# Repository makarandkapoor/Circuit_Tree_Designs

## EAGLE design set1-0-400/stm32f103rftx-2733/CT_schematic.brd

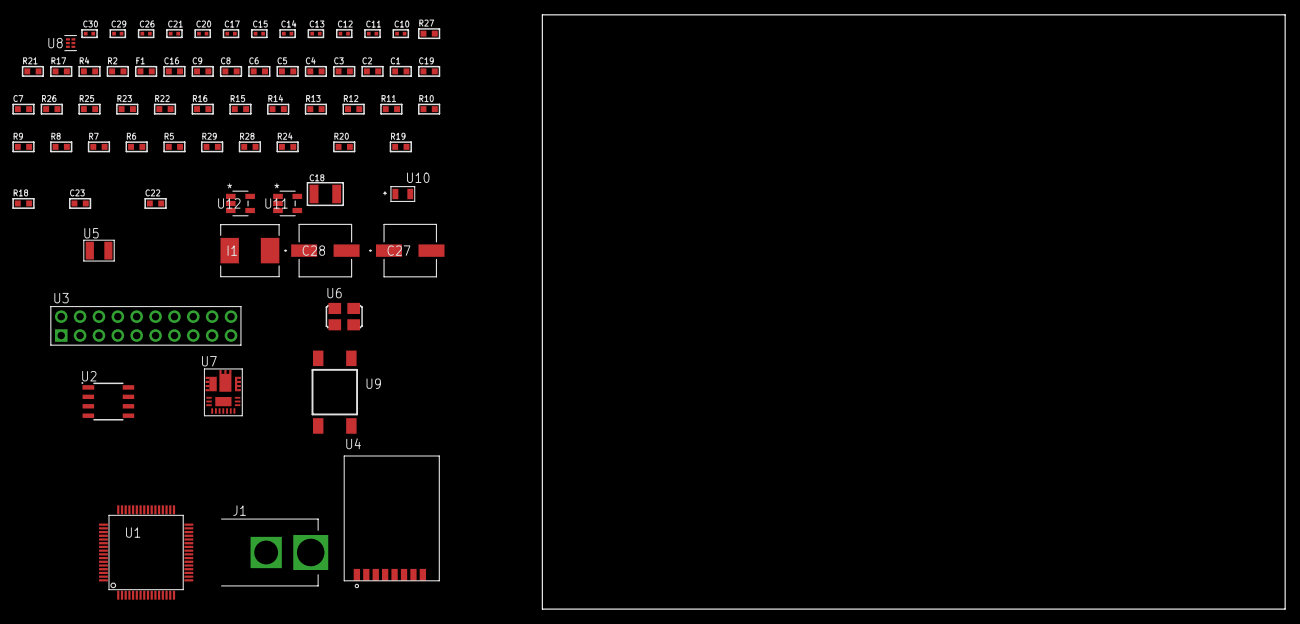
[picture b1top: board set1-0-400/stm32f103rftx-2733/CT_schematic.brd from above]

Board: 2 copper layers, 100.0 x 80.0 mm, 70 parts (0 on the bottom side), 42 nets, no tracks yet.

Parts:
C1, C9, C16: 1e-06; C0603
C2, C3, C4, C5, C6: 1e-07; C0603
C7: 4.7e-06; C0603
C8: 1e-08; C0603
C10, C11: 1e-11; C0402
C12, C17, C29, C30: 1e-08; C0402
C13, C14, C15, C20, C21, C26: 1e-07; C0402
C18: 0.0001; C1210
C19: 2.2e-06; C0603
C22: 8.6971073877236e-09; R0603
C23: 2.9649229730876e-07; R0603
C27, C28: 0.0001; EXV-9H
F1: 240.0; L0603
I1: 6.8e-07; IND25X25CZ
J1: PJ-037B; PJ-037B_PACKAGE
R2: 1000.0; R0603
R4: 4700.0; R0603
R5, R6, R7, R8, R9, R10, R11, R12, R13, R14, R15, R16, R25, R26: 10000.0; R0603
R17: 0.1; R0603
R18: 4030.2416170974; R0603
R19: 719.68600305311; R0603
R20: 58.613333333333; R0603
R21: 130.0; R0603
R22: 39000.0; R0603
R23: 49900.0; R0603
R24: 5147.5789473684; R0603
R27: 9100.0; R0603
R28: 680000.0; R0603
R29: 120000.0; R0603
U1: stm32f103rft7; LQFP64
U2: AT25M02-SSHD-T; SOIC-8
U3: TST-110-05-T-D-RA
U4: RFM75-S
U5: ABS07-32.768KHZ-7-T
U6: ASFL1-25MHZ-NCS; ASFL1
U7: IR3899MTR1PBF
U8: TPS3895ADRYR; SON-6
U9: 4-1437565-2; SW_4-1437565-2
U10: Q65110A2395; LGM67K-G1J2-24-Z
U11, U12: nc7sz125m5x; NC7SZ125M5X

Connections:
CLK_CRYSTAL_U1_3: C10.1, U1.3, U5.1
CLK_CRYSTAL_U1_4: C11.1, U1.4, U5.2
CLK_U1_5: U1.5, U6.3
GND: C1.2, C2.2, C3.2, C4.2, C5.2, C6.2, C7.2, C8.2, C9.2, C10.2, C11.2, C12.2, C13.2, C14.2, C15.2, C16.2, C17.2, C19.2, C20.2, C21.2, C26.2, C27.2, C28.2, C29.2, C30.2, J1.2, R2.2, R5.2, R14.2, R17.1, R17.2, R19.2, R22.2, R24.2, R27.2, R29.2, U1.12, U1.18, U1.31, U1.47, U1.63, U2.4, U3.4, U3.6, U3.8, U3.10, U3.12, U3.14, U3.16, U3.18, U3.20, U4.1, U6.2, U7.4, U7.11, U7.17, U8.2, U10.C, U11.2, U11.3, U12.1, U12.3
NET_U1_7: R4.1, U1.7, U12.4
NET_U1_13: C8.1, C9.1, F1.1, U1.13
NET_U1_60: R5.1, U1.60
NET_U1_62: U9.3, U9.4
NET_U2_3: R6.1, U2.3
NET_U2_7: R8.1, U2.7
NET_U3_3: R9.1, U3.3
NET_U3_7: R11.1, U3.7
NET_U3_9: R12.1, U3.9
NET_U3_19: R14.1, U3.19
NET_U4_3: R15.1, U4.3
NET_U7_1: C22.1, R18.1, R19.1, R20.1, R21.1, U7.1, U7.8
NET_U7_2: C21.1, U7.2
NET_U7_3: C22.2, C23.1, C23.2, U7.3
NET_U7_5: R22.1, U7.5
NET_U7_10: C19.1, U7.10
NET_U7_12: C18.1, I1.1, U7.12
NET_U7_14: C18.2, U7.14
NET_U7_15: R23.1, R24.1, U7.15
NET_U7_ATNET_3: I1.2, R18.2
NET_U7_ATNET_4: C23.2, R20.2
NET_U8_1: R26.1, R27.1, U8.1
NET_U8_3: R28.2, R29.1, U8.3
NET_U8_4: R25.1, U8.4, U11.4, U12.2
NET_U9_1: R2.1, U9.1, U9.2
PROC_SPI1_MISO: U1.22, U4.7
PROC_SPI1_MOSI: U1.23, U4.6
PROC_SPI1_NSS: R16.1, U1.20, U4.4
PROC_SPI1_SCK: U1.21, U4.5
PROC_SPI2_MISO: U1.35, U2.2
PROC_SPI2_MOSI: U1.36, U2.5
PROC_SPI2_NSS: R7.1, U1.33, U2.1
PROC_SPI2_SCK: U1.34, U2.6
PROC_SYS_JTDI: R10.1, U1.50, U3.5
PROC_SYS_JTDO_TRACESWO: U1.55, U3.13
RST_OUT_U3_SRESET_B: R13.1, U3.15, U11.1
VCC_S1_16V8: C20.1, C27.1, C28.1, J1.1, R23.2, U7.9
VCC_TIER1_3V3: C1.1, C2.1, C3.1, C4.1, C5.1, C6.1, C7.1, C12.1, C13.1, C14.1, C15.1, C16.1, C17.1, C26.1, C29.1, C30.1, F1.2, I1.2, R4.2, R6.2, R7.2, R8.2, R9.2, R10.2, R11.2, R12.2, R13.2, R15.2, R16.2, R18.2, R25.2, R26.2, R28.1, U1.1, U1.19, U1.32, U1.48, U1.64, U2.8, U3.1, U3.2, U4.2, U6.4, U8.6, U11.5, U12.5

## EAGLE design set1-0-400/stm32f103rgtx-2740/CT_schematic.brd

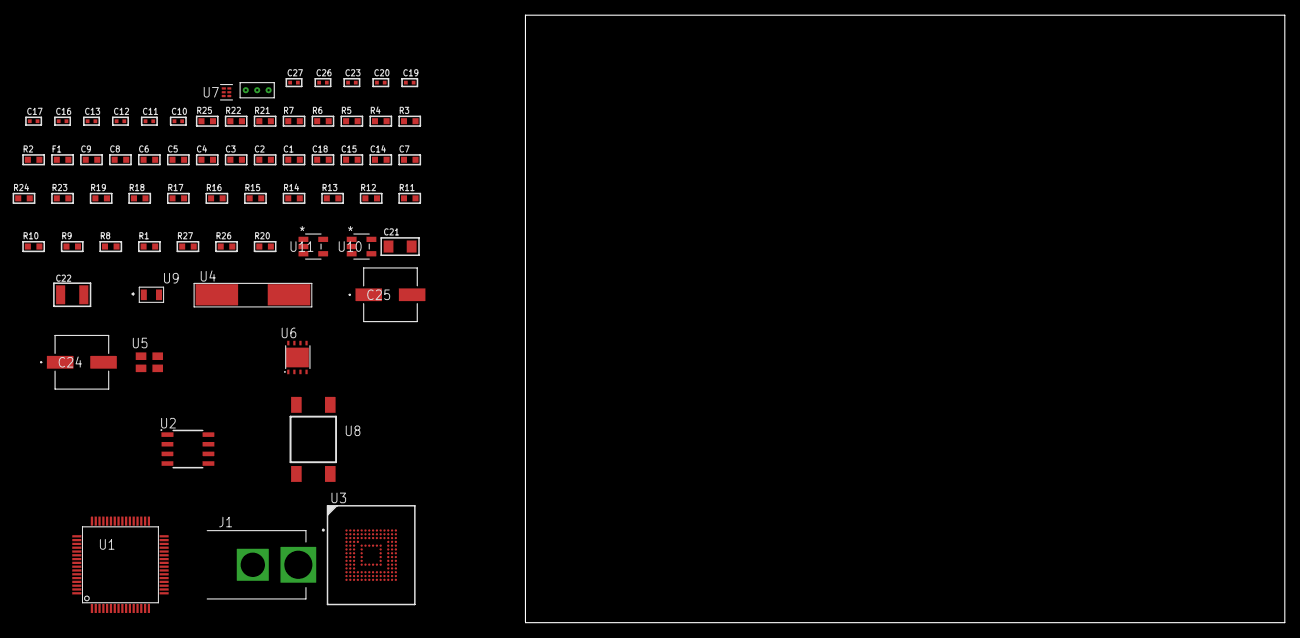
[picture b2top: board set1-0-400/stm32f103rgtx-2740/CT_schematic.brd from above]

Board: 2 copper layers, 100.0 x 80.0 mm, 68 parts (0 on the bottom side), 35 nets, no tracks yet.

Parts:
C1, C9: 1e-06; C0603
C2, C3, C4, C5, C6: 1e-07; C0603
C7: 4.7e-06; C0603
C8: 1e-08; C0603
C10, C11: 1e-11; C0402
C12, C19, C20, C26, C27: 1e-08; C0402
C13, C16, C17, C23: 1e-07; C0402
C14, C15, C18: 2.2e-06; C0603
C21: 1e-05; C1206
C22: 1e-05; C1210
C24, C25: 0.0001; EXV-9H
F1: 240.0; L0603
J1: PJ-037B; PJ-037B_PACKAGE
R1, R8, R9, R23, R24: 10000.0; R0603
R2, R22: 1000.0; R0603
R3: 1600.5; R0603
R4, R5: 4700.0; R0603
R6, R7: 2200.0; R0603
R10, R11, R12, R13, R14, R15, R16, R17, R18, R19: 34000.0; R0603
R20: 100000.0; R0603
R21: 2231.0; R0603
R25: 9100.0; R0603
R26: 680000.0; R0603
R27: 120000.0; R0603
U1: stm32f103rgt7; LQFP64
U2: M24M02-DRMN6TP; SOIC-8
U3: mtfc4gmcdm; TFBGA-153
U4: ABLS-25.000MHZ-B2F-T
U5: ASEK-32.768KHz-ECST; ASEK
U6: LP3878SDX-ADJ/NOPB; WSON-8
U7: TPS3895ADRYR; SON-6
U8: 4-1437565-2; SW_4-1437565-2
U9: Q65110A2395; LGM67K-G1J2-24-Z
U10, U11: nc7sz125m5x; NC7SZ125M5X
U12: Dummy; DUMMY_PACKAGE_153

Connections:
CLK_CRYSTAL_U1_5: C10.1, U1.5, U4.1
CLK_CRYSTAL_U1_6: C11.1, U1.6, U4.2
CLK_U1_3: U1.3, U5.3
GND: C1.2, C2.2, C3.2, C4.2, C5.2, C6.2, C7.2, C8.2, C9.2, C10.2, C11.2, C12.2, C13.2, C14.2, C15.2, C16.2, C17.2, C18.2, C19.2, C20.2, C21.2, C22.2, C23.2, C24.2, C25.2, C26.2, C27.2, J1.2, R2.2, R8.2, R9.2, R22.2, R25.2, R27.2, U1.12, U1.18, U1.31, U1.47, U1.63, U2.4, U3.C4, U3.E7, U3.G5, U3.H10, U3.K8, U3.N2, U3.N5, U3.P4, U3.P6, U5.2, U6.3, U6.PAD, U7.2, U9.C, U10.1, U10.3, U11.1, U11.3, U12.1
NET_U1_7: R5.1, U1.7, U11.4
NET_U1_13: C8.1, C9.1, F1.1, U1.13
NET_U1_56: R3.1, U1.56, U9.A
NET_U1_57: R1.1, U1.57, U8.3, U8.4
NET_U1_58: R6.1, U1.58, U2.6
NET_U1_59: R7.1, U1.59, U2.5
NET_U1_60: R8.1, U1.60
NET_U2_3: R9.1, U2.3
NET_U3_C2: C15.1, C16.1, U3.C2
NET_U3_K5: R4.1, U3.K5, U10.4
NET_U6_1: C20.1, U6.1
NET_U6_6: R21.2, R22.1, U6.6
NET_U6_8: R20.1, U6.8
NET_U7_1: R24.1, R25.1, U7.1
NET_U7_3: R26.2, R27.1, U7.3
NET_U7_4: R23.1, U7.4, U10.2, U11.2
NET_U8_1: R2.1, U8.1, U8.2
PROC_SDIO_CK: R19.1, U1.53, U3.M6
PROC_SDIO_CMD: R18.1, U1.54, U3.M5
PROC_SDIO_D0: R10.1, U1.39, U3.A3
PROC_SDIO_D1: R11.1, U1.40, U3.A4
PROC_SDIO_D2: R12.1, U1.51, U3.A5
PROC_SDIO_D3: R13.1, U1.52, U3.B2
PROC_SDIO_D4: R14.1, U1.61, U3.B3
PROC_SDIO_D5: R15.1, U1.62, U3.B4
PROC_SDIO_D6: R16.1, U1.37, U3.B5
PROC_SDIO_D7: R17.1, U1.38, U3.B6
PROC_TIM1_CH2: U1.42, U12.2
PROC_TIM1_CH4: U1.44, U12.3
VCC_S1_6V1: C21.1, C24.1, C25.1, J1.1, R20.2, U6.4
VCC_TIER1_3V3: C1.1, C2.1, C3.1, C4.1, C5.1, C6.1, C7.1, C12.1, C13.1, C14.1, C17.1, C18.1, C19.1, C22.1, C23.1, C26.1, C27.1, F1.2, R1.2, R3.2, R4.2, R5.2, R6.2, R7.2, R10.2, R11.2, R12.2, R13.2, R14.2, R15.2, R16.2, R17.2, R18.2, R19.2, R21.1, R23.2, R24.2, R26.1, U1.1, U1.19, U1.32, U1.48, U1.64, U2.8, U3.C6, U3.E6, U3.F5, U3.J10, U3.K9, U3.M4, U3.N4, U3.P3, U3.P5, U5.4, U6.5, U7.6, U10.5, U11.5

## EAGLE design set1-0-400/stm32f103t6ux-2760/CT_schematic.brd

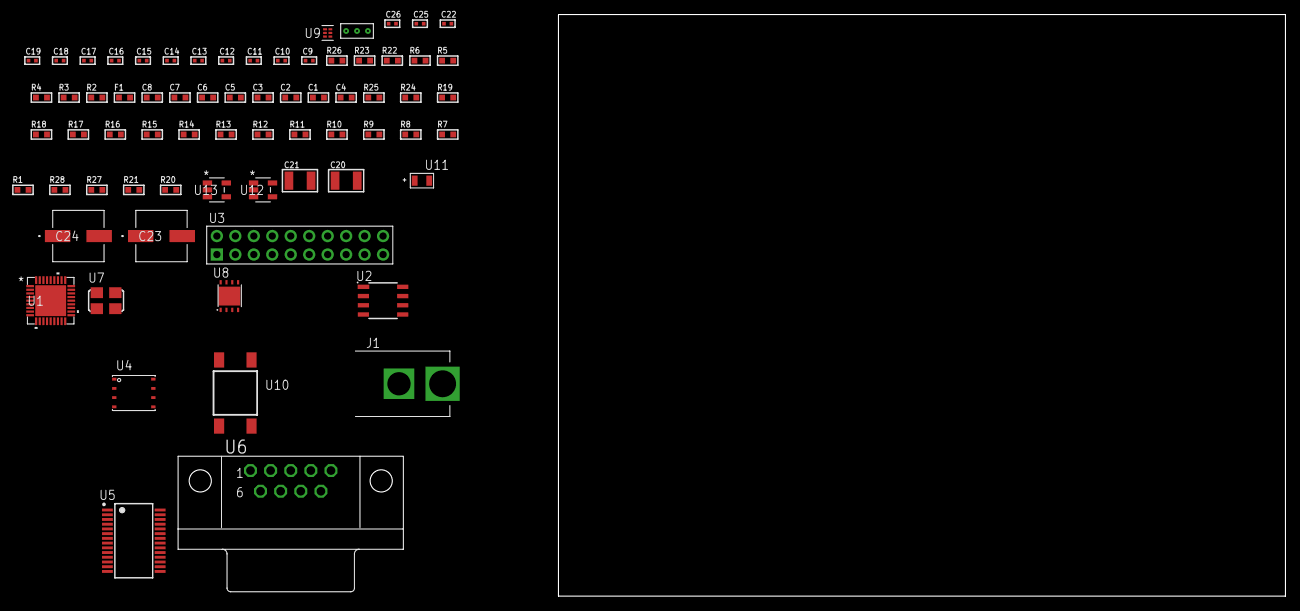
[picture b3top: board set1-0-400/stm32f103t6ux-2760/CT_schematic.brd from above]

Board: 2 copper layers, 100.0 x 80.0 mm, 70 parts (0 on the bottom side), 51 nets, no tracks yet.

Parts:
C1, C2, C3, C5, C6: 1e-07; C0603
C4: 4.7e-06; C0603
C7: 1e-08; C0603
C8: 1e-06; C0603
C9, C12, C18, C19, C25, C26: 1e-08; C0402
C10, C11, C13, C14, C15, C16, C17, C22: 1e-07; C0402
C20, C21: 1e-05; C1210
C23, C24: 0.0001; EXV-9H
F1: 240.0; L0603
J1: PJ-037B; PJ-037B_PACKAGE
R1, R7, R8, R9, R10, R11, R12, R13, R14, R15, R16, R17, R18, R19, R24, R25: 10000.0; R0603
R2, R23: 1000.0; R0603
R3: 1600.5; R0603
R4: 4700.0; R0603
R5, R6: 2200.0; R0603
R20, R21: 100000.0; R0603
R22: 2231.0; R0603
R26: 9100.0; R0603
R27: 680000.0; R0603
R28: 120000.0; R0603
U1: stm32f103t6u7; VFQFPN36
U2: AT25320B-SSHL-T; SOIC-8
U3: TST-110-05-T-D-RA
U4: 24AA256-I/MF; DFN8-S
U5: ST3241EBPR; SSOP-28
U6: 182-009-113R531; 182-009-MALE
U7: ASFL1-25MHZ-NCS; ASFL1
U8: LP3878SDX-ADJ/NOPB; WSON-8
U9: TPS3895ADRYR; SON-6
U10: 4-1437565-2; SW_4-1437565-2
U11: Q65110A2395; LGM67K-G1J2-24-Z
U12, U13: nc7sz125m5x; NC7SZ125M5X
U14: Dummy; DUMMY_PACKAGE_149

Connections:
CLK_U1_2: U1.2, U7.3
GND: C1.2, C2.2, C3.2, C4.2, C5.2, C6.2, C7.2, C8.2, C9.2, C10.2, C11.2, C12.2, C13.2, C16.2, C17.2, C18.2, C19.2, C20.2, C21.2, C22.2, C23.2, C24.2, C25.2, C26.2, J1.2, R2.2, R7.2, R16.2, R17.2, R18.2, R23.2, R26.2, R28.2, U1.5, U1.18, U1.26, U1.36, U1.37, U2.4, U3.4, U3.6, U3.8, U3.10, U3.12, U3.14, U3.16, U3.18, U3.20, U4.4, U5.23, U5.25, U6.5, U7.2, U8.3, U8.PAD, U9.2, U11.C, U12.2, U12.3, U13.1, U13.3, U14.1
NET_U1_4: R4.1, U1.4, U13.4
NET_U1_6: C7.1, C8.1, F1.1, U1.6
NET_U1_31: R3.1, U1.31, U11.A
NET_U1_32: R1.1, U1.32, U10.3, U10.4
NET_U1_33: R5.1, U1.33, U4.6
NET_U1_34: R6.1, U1.34, U4.5
NET_U1_35: R7.1, U1.35
NET_U2_3: R8.1, U2.3
NET_U2_7: R10.1, U2.7
NET_U3_3: R11.1, U3.3
NET_U3_7: R13.1, U3.7
NET_U3_9: R14.1, U3.9
NET_U3_19: R16.1, U3.19
NET_U4_1: R17.1, U4.1
NET_U4_2: R18.1, U4.2
NET_U4_3: R19.1, U4.3
NET_U5_1: C15.1, U5.1
NET_U5_2: C15.2, U5.2
NET_U5_3: C17.1, U5.3
NET_U5_22: R20.1, U5.22
NET_U5_24: C14.2, U5.24
NET_U5_27: C16.1, U5.27
NET_U5_28: C14.1, U5.28
NET_U6_2: U5.4, U6.2
NET_U6_3: U5.9, U6.3
NET_U6_7: U5.5, U6.7
NET_U6_8: U5.10, U6.8
NET_U8_1: C19.1, U8.1
NET_U8_6: R22.2, R23.1, U8.6
NET_U8_8: R21.1, U8.8
NET_U9_1: R25.1, R26.1, U9.1
NET_U9_3: R27.2, R28.1, U9.3
NET_U9_4: R24.1, U9.4, U12.4, U13.2
NET_U10_1: R2.1, U10.1, U10.2
PROC_SPI1_MISO: U1.13, U2.2
PROC_SPI1_MOSI: U1.14, U2.5
PROC_SPI1_NSS: R9.1, U1.11, U2.1
PROC_SPI1_SCK: U1.12, U2.6
PROC_SYS_JTDI: R12.1, U1.29, U3.5
PROC_SYS_JTDO_TRACESWO: U1.30, U3.13
PROC_TIM1_CH2N: U1.15, U14.3
PROC_TIM1_CH3N: U1.16, U14.2
PROC_USART1_CTS: U1.23, U5.13
PROC_USART1_RTS: U1.24, U5.18
PROC_USART1_RX: U1.22, U5.19
PROC_USART1_TX: U1.21, U5.14
RST_OUT_U3_SRESET_B: R15.1, U3.15, U12.1
VCC_S1_14V9: C20.1, C23.1, C24.1, J1.1, R21.2, U8.4
VCC_TIER1_3V3: C1.1, C2.1, C3.1, C4.1, C5.1, C6.1, C9.1, C10.1, C11.1, C12.1, C13.1, C18.1, C21.1, C22.1, C25.1, C26.1, F1.2, R1.2, R3.2, R4.2, R5.2, R6.2, R8.2, R9.2, R10.2, R11.2, R12.2, R13.2, R14.2, R15.2, R19.2, R20.2, R22.1, R24.2, R25.2, R27.1, U1.1, U1.19, U1.27, U2.8, U3.1, U3.2, U4.7, U4.8, U5.26, U7.4, U8.5, U9.6, U12.5, U13.5

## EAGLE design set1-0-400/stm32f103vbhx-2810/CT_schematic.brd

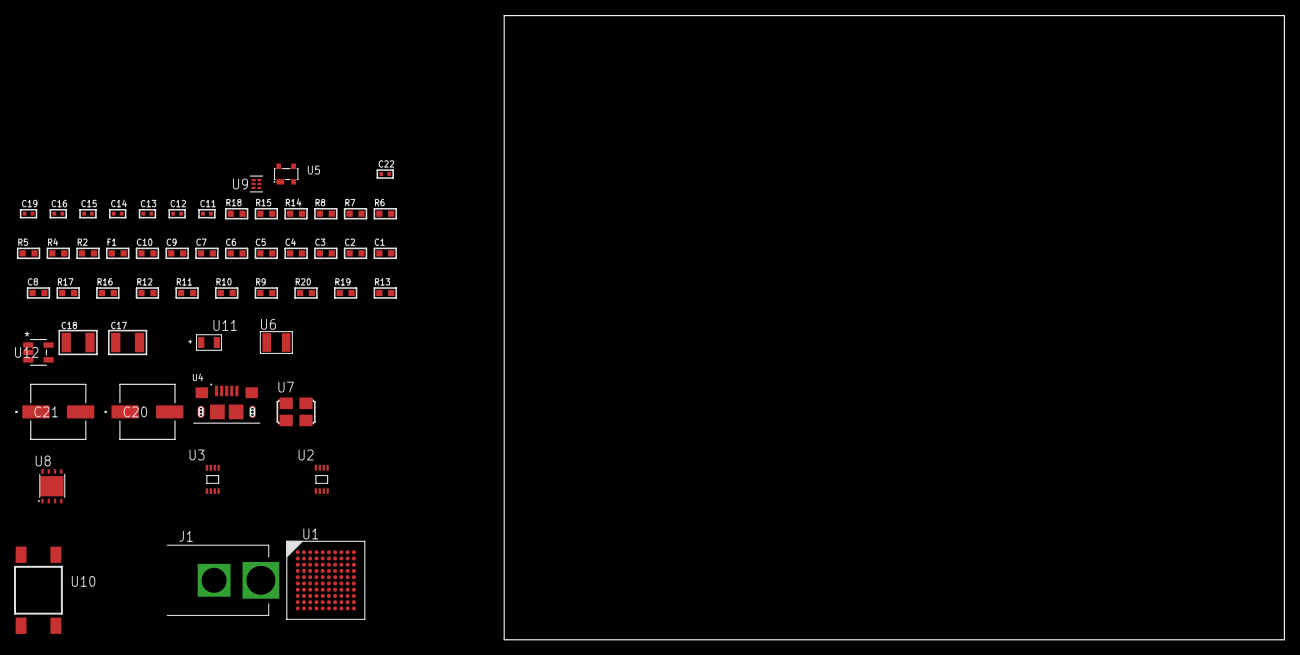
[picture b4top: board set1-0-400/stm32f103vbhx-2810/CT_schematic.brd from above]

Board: 2 copper layers, 54 parts (0 on the bottom side), 27 nets, no tracks yet.

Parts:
C1, C10: 1e-06; C0603
C2, C3, C4, C5, C6, C7: 1e-07; C0603
C8: 4.7e-06; C0603
C9: 1e-08; C0603
C11, C12: 1e-11; C0402
C13, C14, C15, C16, C22: 1e-08; C0402
C17, C18: 1e-05; C1210
C19: 1e-07; C0402
C20, C21: 0.0001; EXV-9H
F1: 240.0; L0603
J1: PJ-037B; PJ-037B_PACKAGE
R2, R15: 1000.0; R0603
R4: 4700.0; R0603
R5, R6, R7, R8: 2200.0; R0603
R9, R10, R11, R12, R16, R17: 10000.0; R0603
R13: 100000.0; R0603
R14: 2231.0; R0603
R18: 9100.0; R0603
R19: 680000.0; R0603
R20: 120000.0; R0603
U1: stm32f103vbh7; LFBGA100
U2: 24AA08T-I/MNY; TDFN-8/6MM
U3: 24AA64T-I/MNY; TDFN-8/6MM
U4: 10118193-0001LF; FCI_10118193-0001LF
U5: prtr5v0u2ax; SOT143B
U6: ABS07-32.768KHZ-7-T
U7: ASFL1-25MHZ-NCS; ASFL1
U8: LP3878SDX-ADJ/NOPB; WSON-8
U9: TPS3895ADRYR; SON-6
U10: 4-1437565-2; SW_4-1437565-2
U11: Q65110A2395; LGM67K-G1J2-24-Z
U12: nc7sz125m5x; NC7SZ125M5X

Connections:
CLK_CRYSTAL_U1_A1: C11.1, U1.A1, U6.1
CLK_CRYSTAL_U1_B1: C12.1, U1.B1, U6.2
CLK_U1_C1: U1.C1, U7.3
GND: C1.2, C2.2, C3.2, C4.2, C5.2, C6.2, C7.2, C8.2, C9.2, C10.2, C11.2, C12.2, C13.2, C14.2, C15.2, C16.2, C17.2, C18.2, C19.2, C20.2, C21.2, C22.2, J1.2, R2.2, R9.2, R10.2, R11.2, R15.2, R18.2, R20.2, U1.C2, U1.E4, U1.E5, U1.E6, U1.E7, U1.G1, U1.H1, U2.4, U2.7, U3.4, U3.7, U4.5, U4.6, U4.7, U4.8, U4.9, U5.1, U7.2, U8.3, U8.PAD, U9.2, U11.C, U12.1, U12.3
NET_U1_A4: R6.1, U1.A4, U2.5
NET_U1_B4: R5.1, U1.B4, U2.6
NET_U1_D5: R9.1, U1.D5
NET_U1_E1: R4.1, U1.E1, U12.4
NET_U1_J7: R7.1, U1.J7, U3.6
NET_U1_K1: C9.1, C10.1, F1.1, U1.J1, U1.K1
NET_U1_K7: R8.1, U1.K7, U3.5
NET_U1_K10: U10.3, U10.4
NET_U3_1: R10.1, U3.1
NET_U3_2: R11.1, U3.2
NET_U3_3: R12.1, U3.3
NET_U5_4: U4.1, U5.4
NET_U8_1: C16.1, U8.1
NET_U8_6: R14.2, R15.1, U8.6
NET_U8_8: R13.1, U8.8
NET_U9_1: R17.1, R18.1, U9.1
NET_U9_3: R19.2, R20.1, U9.3
NET_U9_4: R16.1, U9.4, U12.2
NET_U10_1: R2.1, U10.1, U10.2
PROC_USB_DM: U1.C10, U4.2, U5.3
PROC_USB_DP: U1.B10, U4.3, U5.2
VCC_S1_14V8: C17.1, C20.1, C21.1, J1.1, R13.2, U8.4
VCC_TIER1_3V3: C1.1, C2.1, C3.1, C4.1, C5.1, C6.1, C7.1, C8.1, C13.1, C14.1, C15.1, C18.1, C19.1, C22.1, F1.2, R4.2, R5.2, R6.2, R7.2, R8.2, R12.2, R14.1, R16.2, R17.2, R19.1, U1.B2, U1.D2, U1.F4, U1.F5, U1.F6, U1.F7, U2.8, U3.8, U7.4, U8.5, U9.6, U12.5

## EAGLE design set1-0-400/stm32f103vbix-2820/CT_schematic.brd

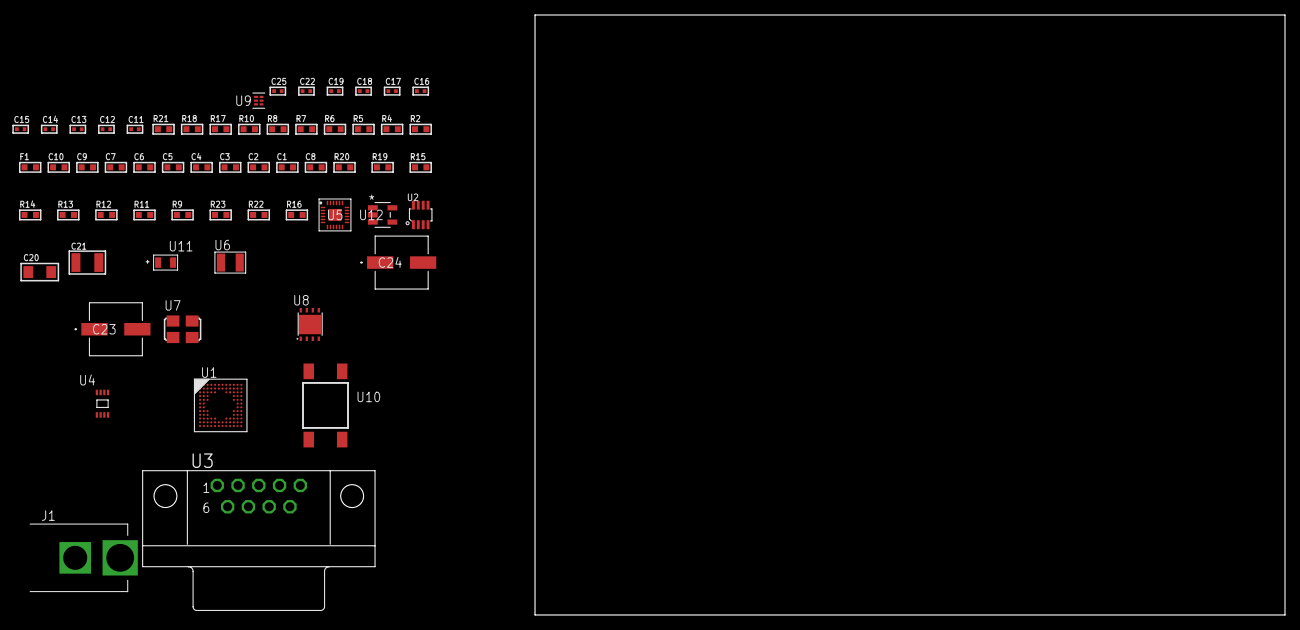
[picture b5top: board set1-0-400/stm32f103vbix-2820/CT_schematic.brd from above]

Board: 2 copper layers, 100.0 x 80.0 mm, 60 parts (0 on the bottom side), 34 nets, no tracks yet.

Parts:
C1, C10: 1e-06; C0603
C2, C3, C4, C5, C6, C7: 1e-07; C0603
C8: 4.7e-06; C0603
C9: 1e-08; C0603
C11, C12: 1e-11; C0402
C13, C15, C16, C22: 1e-07; C0402
C14, C17, C18, C19, C25: 1e-08; C0402
C20: 1e-05; C1206
C21: 1e-05; C1210
C23, C24: 0.0001; EXV-9H
F1: 240.0; L0603
J1: PJ-037B; PJ-037B_PACKAGE
R2, R18: 1000.0; R0603
R4: 4700.0; R0603
R5, R6, R7, R8: 2200.0; R0603
R9, R11, R12, R13, R14, R15, R19, R20: 10000.0; R0603
R10: 120.0; R0603
R16: 100000.0; R0603
R17: 2231.0; R0603
R21: 9100.0; R0603
R22: 680000.0; R0603
R23: 120000.0; R0603
U1: stm32f103vbi6; UFBGA100
U2: MAX3051EKA+T; SOT-23-8
U3: 182-009-113R531; 182-009-MALE
U4: 24AA32AT-I/MNY; TDFN-8/6MM
U5: MPU-9250; QFN24_2
U6: ABS07-32.768KHZ-7-T
U7: ASFL1-25MHZ-NCS; ASFL1
U8: LP3878SDX-ADJ/NOPB; WSON-8
U9: TPS3895ADRYR; SON-6
U10: 4-1437565-2; SW_4-1437565-2
U11: Q65110A2395; LGM67K-G1J2-24-Z
U12: nc7sz125m5x; NC7SZ125M5X

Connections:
CLK_CRYSTAL_U1_D1: C11.1, U1.D1, U6.1
CLK_CRYSTAL_U1_E1: C12.1, U1.E1, U6.2
CLK_U1_F1: U1.F1, U7.3
GND: C1.2, C2.2, C3.2, C4.2, C5.2, C6.2, C7.2, C8.2, C9.2, C10.2, C11.2, C12.2, C13.2, C14.2, C15.2, C16.2, C17.2, C18.2, C19.2, C20.2, C21.2, C22.2, C23.2, C24.2, C25.2, J1.2, R2.2, R9.2, R13.2, R18.2, R21.2, R23.2, U1.D3, U1.E3, U1.F2, U1.F11, U1.F12, U1.J1, U1.K1, U2.2, U2.8, U3.5, U4.4, U4.7, U5.18, U5.20, U5.25, U7.2, U8.3, U8.PAD, U9.2, U11.C, U12.1, U12.3
NET_U1_A3: R5.1, U1.A3, U5.23
NET_U1_A4: R9.1, U1.A4
NET_U1_B3: R6.1, U1.B3, U5.24
NET_U1_H2: R4.1, U1.H2, U12.4
NET_U1_L10: R7.1, U1.L10, U4.6
NET_U1_L11: R8.1, U1.L11, U4.5
NET_U1_M1: C9.1, C10.1, F1.1, U1.L1, U1.M1
NET_U1_M12: U10.3, U10.4
NET_U2_6: R10.2, U2.6
NET_U3_2: R10.2, U2.6, U3.2
NET_U3_3: R10.1, U2.7, U3.3
NET_U4_1: R11.1, U4.1
NET_U4_2: R12.1, U4.2
NET_U4_3: R13.1, U4.3
NET_U5_9: R15.1, U5.9
NET_U5_10: C15.1, U5.10
NET_U5_22: R14.1, U5.22
NET_U8_1: C19.1, U8.1
NET_U8_6: R17.2, R18.1, U8.6
NET_U8_8: R16.1, U8.8
NET_U9_1: R20.1, R21.1, U9.1
NET_U9_3: R22.2, R23.1, U9.3
NET_U9_4: R19.1, U9.4, U12.2
NET_U10_1: R2.1, U10.1, U10.2
PROC_CAN_RX: U1.B12, U2.4
PROC_CAN_TX: U1.A12, U2.1
PROC_GPIO_TO_U5_FSYNC: U1.A2, U5.11
PROC_GPIO_TO_U5_INT_B: U1.A1, U5.12
VCC_S1_9V4: C20.1, C23.1, C24.1, J1.1, R16.2, U8.4
VCC_TIER1_3V3: C1.1, C2.1, C3.1, C4.1, C5.1, C6.1, C7.1, C8.1, C13.1, C14.1, C16.1, C17.1, C18.1, C21.1, C22.1, C25.1, F1.2, R4.2, R5.2, R6.2, R7.2, R8.2, R11.2, R12.2, R14.2, R15.2, R17.1, R19.2, R20.2, R22.1, U1.C4, U1.E2, U1.G2, U1.G11, U1.G12, U1.H3, U2.3, U4.8, U5.1, U5.8, U5.13, U7.4, U8.5, U9.6, U12.5

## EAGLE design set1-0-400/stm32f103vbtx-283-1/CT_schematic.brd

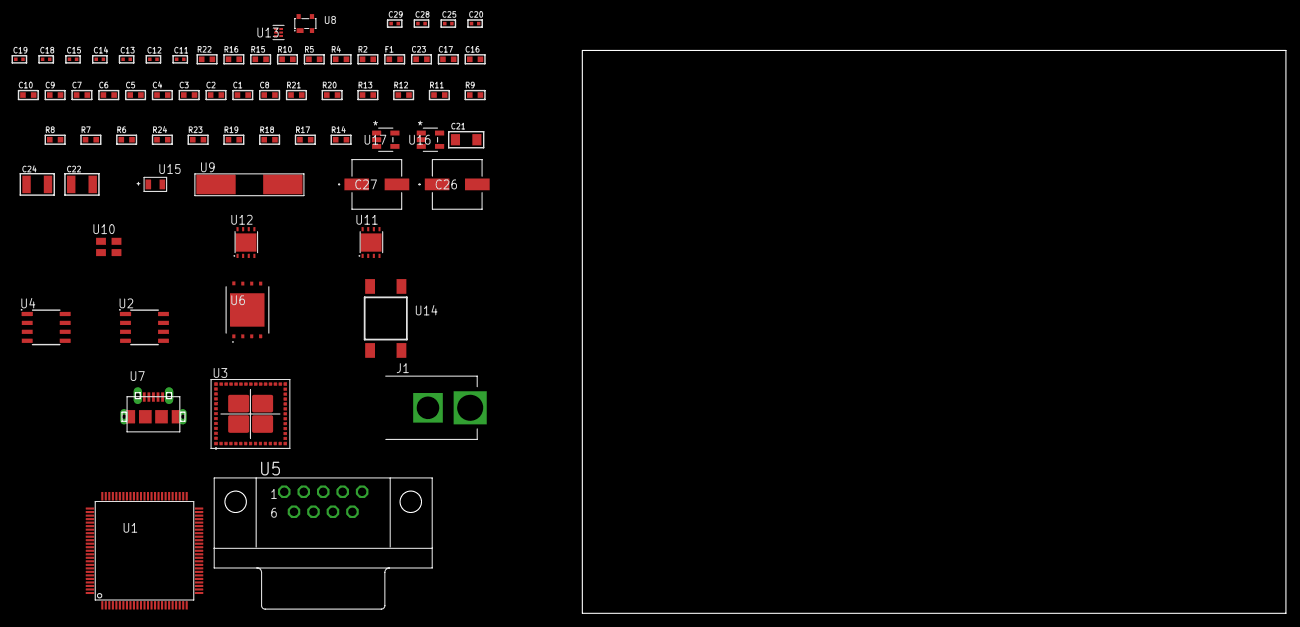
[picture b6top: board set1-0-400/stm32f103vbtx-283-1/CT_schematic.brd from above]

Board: 2 copper layers, 70 parts (0 on the bottom side), 45 nets, no tracks yet.

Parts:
C1, C10, C16, C17, C23: 1e-06; C0603
C2, C3, C4, C5, C6, C7: 1e-07; C0603
C8: 4.7e-06; C0603
C9: 1e-08; C0603
C11, C12: 1e-11; C0402
C13, C18, C19, C20, C28, C29: 1e-08; C0402
C14, C15, C25: 1e-07; C0402
C21: 1e-05; C1206
C22, C24: 1e-05; C1210
C26, C27: 0.0001; EXV-9H
F1: 240.0; L0603
J1: PJ-037B; PJ-037B_PACKAGE
R2, R16: 1000.0; R0603
R4, R5: 4700.0; R0603
R6, R7, R8, R9, R11, R12, R13, R20, R21: 10000.0; R0603
R10: 120.0; R0603
R14, R17, R19: 100000.0; R0603
R15: 2231.0; R0603
R18: 300000.0; R0603
R22: 9100.0; R0603
R23: 680000.0; R0603
R24: 120000.0; R0603
U1: stm32f103vbt7; LQFP100
U2: AT25160B-SSHL-T; SOIC-8
U3: MBH7BLZ02-109004
U4: MCP2562-E/SN; SOIC-8
U5: 182-009-113R531; 182-009-MALE
U6: S25FL128SDPNFI001; WNG008
U7: 47590-0001; MICRO_USB_AB
U8: prtr5v0u2ax; SOT143B
U9: ABLS-25.000MHZ-B2F-T
U10: ASEK-32.768KHz-ECST; ASEK
U11: LP3878SDX-ADJ/NOPB; WSON-8
U12: LP2951ACSDX/NOPB; WSON-8
U13: TPS3895ADRYR; SON-6
U14: 4-1437565-2; SW_4-1437565-2
U15: Q65110A2395; LGM67K-G1J2-24-Z
U16, U17: nc7sz125m5x; NC7SZ125M5X

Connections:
CLK_CRYSTAL_U1_12: C11.1, U1.12, U9.1
CLK_CRYSTAL_U1_13: C12.1, U1.13, U9.2
CLK_U1_8: U1.8, U10.3
GND: C1.2, C2.2, C3.2, C4.2, C5.2, C6.2, C7.2, C8.2, C9.2, C10.2, C11.2, C12.2, C13.2, C14.2, C15.2, C16.2, C17.2, C18.2, C19.2, C20.2, C21.2, C22.2, C23.2, C24.2, C25.2, C26.2, C27.2, C28.2, C29.2, J1.2, R2.2, R6.2, R16.2, R19.2, R22.2, R24.2, U1.10, U1.19, U1.20, U1.27, U1.49, U1.74, U1.99, U2.4, U3.1, U3.3, U3.15, U3.27, U3.29, U3.41, U3.42, U3.43, U3.44, U3.45, U3.46, U3.47, U3.48, U3.49, U3.50, U3.52, U3.53, U3.54, U3.55, U3.56, U4.2, U4.8, U5.5, U6.4, U6.PAD, U7.5, U7.6, U7.7, U7.8, U7.9, U8.1, U10.2, U11.3, U11.PAD, U12.3, U12.4, U12.PAD, U13.2, U15.C, U16.1, U16.3, U17.1, U17.3
NET_U1_14: R5.1, U1.14, U17.4
NET_U1_22: C9.1, C10.1, F1.1, U1.21, U1.22
NET_U1_94: R6.1, U1.94
NET_U1_98: U14.3, U14.4
NET_U2_3: R7.1, U2.3
NET_U2_7: R9.1, U2.7
NET_U3_39: R4.1, U3.39, U16.4
NET_U4_6: R10.2, U4.6
NET_U5_2: R10.2, U4.6, U5.2
NET_U5_3: R10.1, U4.7, U5.3
NET_U6_3: R11.1, U6.3
NET_U6_7: R13.1, U6.7
NET_U8_4: U7.1, U8.4
NET_U11_1: C20.1, U11.1
NET_U11_6: R15.2, R16.1, U11.6
NET_U11_8: R14.1, U11.8
NET_U12_5: R17.1, U12.5
NET_U12_7: R18.2, R19.1, U12.7
NET_U13_1: R21.1, R22.1, U13.1
NET_U13_3: R23.2, R24.1, U13.3
NET_U13_4: R20.1, U13.4, U16.2, U17.2
NET_U14_1: R2.1, U14.1, U14.2
PROC_CAN_RX: U1.81, U4.4
PROC_CAN_TX: U1.82, U4.1
PROC_SPI1_MISO: U1.31, U6.2
PROC_SPI1_MOSI: U1.32, U6.5
PROC_SPI1_NSS: R12.1, U1.29, U6.1
PROC_SPI1_SCK: U1.30, U6.6
PROC_SPI2_MISO: U1.53, U2.2
PROC_SPI2_MOSI: U1.54, U2.5
PROC_SPI2_NSS: R8.1, U1.51, U2.1
PROC_SPI2_SCK: U1.52, U2.6
PROC_USART2_CTS: U1.23, U3.26
PROC_USART2_RTS: U1.24, U3.24
PROC_USART2_RX: U1.26, U3.25
PROC_USART2_TX: U1.25, U3.23
PROC_USB_DM: U1.70, U7.2, U8.3
PROC_USB_DP: U1.71, U7.3, U8.2
VCC_S1_8V5: C21.1, C23.1, C26.1, C27.1, J1.1, R14.2, U11.4, U12.8
VCC_TIER1_3V3: C1.1, C2.1, C3.1, C4.1, C5.1, C6.1, C7.1, C8.1, C13.1, C14.1, C15.1, C17.1, C18.1, C19.1, C22.1, C25.1, C28.1, C29.1, F1.2, R4.2, R5.2, R7.2, R8.2, R9.2, R11.2, R12.2, R13.2, R15.1, R20.2, R21.2, R23.1, U1.6, U1.11, U1.28, U1.50, U1.75, U1.100, U2.8, U3.28, U4.5, U6.8, U10.4, U11.5, U13.6, U16.5, U17.5
VCC_TIER1_5V0: C16.1, C24.1, R17.2, R18.1, U4.3, U12.1

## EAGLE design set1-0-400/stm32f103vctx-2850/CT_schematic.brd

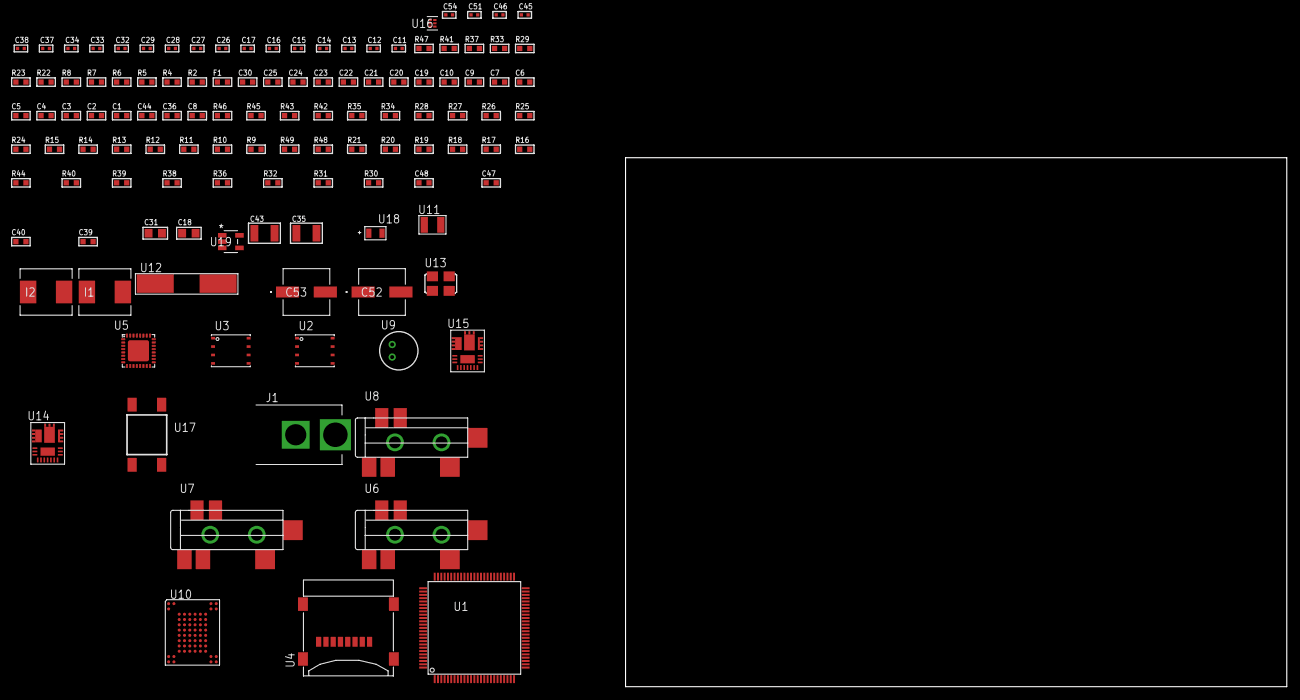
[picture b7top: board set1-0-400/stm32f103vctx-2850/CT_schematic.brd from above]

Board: 2 copper layers, 100.0 x 80.0 mm, 120 parts (0 on the bottom side), 82 nets, no tracks yet.

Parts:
C1, C10, C19, C20, C21, C22, C23, C24, C25, C30: 1e-06; C0603
C2, C3, C4, C5, C6, C7: 1e-07; C0603
C8: 4.7e-06; C0603
C9: 1e-08; C0603
C11, C12, C13, C14: 1e-11; C0402
C15, C16, C34, C54: 1e-08; C0402
C17, C26, C27, C28, C29, C32, C33, C37, C38, C45, C46, C51: 1e-07; C0402
C18, C31: 1e-05; C0805
C35, C43: 0.0001; C1210
C36, C44: 2.2e-06; C0603
C39, C47: 8.6971073877236e-09; R0603
C40, C48: 2.9649229730876e-07; R0603
C52, C53: 0.0001; EXV-9H
F1: 240.0; L0603
I1, I2: 6.8e-07; IND25X25CZ
J1: PJ-037B; PJ-037B_PACKAGE
R2: 1000.0; R0603
R4: 4700.0; R0603
R5, R6, R7, R8: 2200.0; R0603
R9, R10, R11, R12, R13, R14, R15, R24, R25, R26, R27, R28, R45, R46: 10000.0; R0603
R16, R17, R18, R19, R20, R21: 100000.0; R0603
R22, R23: 1270.0; R0603
R29, R37: 0.1; R0603
R30, R38: 4030.2416170974; R0603
R31: 2878.7440122125; R0603
R32, R40: 58.613333333333; R0603
R33, R41: 130.0; R0603
R34, R42: 39000.0; R0603
R35, R43: 49900.0; R0603
R36, R44: 5147.5789473684; R0603
R39: 719.68600305311; R0603
R47: 9100.0; R0603
R48: 680000.0; R0603
R49: 120000.0; R0603
U1: stm32f103vct6; LQFP100
U2: 24AA256-I/MF; DFN8-S
U3: 24AA512-I/MF; DFN8-S
U4: 0472192001; MOLEX_47219-2001
U5: SGTL5000XNAA3; QFN-32
U6, U7, U8: SJ-43515TS-SMT-TR
U9: WM-64PCT; WM-64PC
U10: TH58NVG3S0HBAI4
U11: ABS07-32.768KHZ-7-T
U12: ABLS-25.000MHZ-B2F-T
U13: ASFL-24.57MHZ-NCS; ASFL1
U14, U15: IR3899MTR1PBF
U16: TPS3895ADRYR; SON-6
U17: 4-1437565-2; SW_4-1437565-2
U18: Q65110A2395; LGM67K-G1J2-24-Z
U19: nc7sz125m5x; NC7SZ125M5X

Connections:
CLK_CRYSTAL_U1_8: C11.1, U1.8, U11.1
CLK_CRYSTAL_U1_9: C12.1, U1.9, U11.2
CLK_CRYSTAL_U1_12: C13.1, U1.12, U12.1
CLK_CRYSTAL_U1_13: C14.1, U1.13, U12.2
CLK_U5_21: U5.21, U13.3
GND: C1.2, C2.2, C3.2, C4.2, C5.2, C6.2, C7.2, C8.2, C9.2, C10.2, C11.2, C12.2, C13.2, C14.2, C15.2, C16.2, C17.2, C18.2, C26.2, C27.2, C28.2, C29.2, C30.2, C31.2, C32.2, C33.2, C34.2, C36.2, C37.2, C38.2, C44.2, C45.2, C46.2, C51.2, C52.2, C53.2, C54.2, J1.2, R2.2, R9.2, R10.2, R11.2, R14.2, R15.2, R23.2, R29.1, R29.2, R31.2, R34.2, R36.2, R37.1, R37.2, R39.2, R42.2, R44.2, R47.2, R49.2, U1.10, U1.19, U1.20, U1.27, U1.49, U1.74, U1.99, U2.4, U2.7, U3.4, U4.6, U4.G1, U4.G2, U4.G3, U4.G4, U5.1, U5.3, U5.7, U5.EXP, U7.1, U8.1, U9.2, U10.C5, U10.K3, U10.K8, U13.2, U14.4, U14.11, U14.17, U15.4, U15.11, U15.17, U16.2, U18.C, U19.1, U19.3
NET_U1_14: R4.1, U1.14, U19.4
NET_U1_22: C9.1, C10.1, F1.1, U1.21, U1.22
NET_U1_47: R7.1, U1.47, U3.6
NET_U1_48: R8.1, U1.48, U3.5
NET_U1_92: R5.1, U1.92, U2.6
NET_U1_93: R6.1, U1.93, U2.5
NET_U1_94: R9.1, U1.94
NET_U1_98: U17.3, U17.4
NET_U2_1: R10.1, U2.1
NET_U2_2: R11.1, U2.2
NET_U2_3: R12.1, U2.3
NET_U3_1: R13.1, U3.1
NET_U3_2: R14.1, U3.2
NET_U3_3: R15.1, U3.3
NET_U5_10: C29.1, U5.10
NET_U5_29: R22.1, U5.29
NET_U5_31: R23.1, U5.31
NET_U6_1: U5.4, U6.1
NET_U6_2: U5.2, U6.2
NET_U6_5: U5.6, U6.5
NET_U7_2: C20.1, U7.2
NET_U7_5: C19.1, U7.5
NET_U8_2: C22.1, C23.1, U8.2
NET_U8_5: C21.1, U8.5
NET_U8_13: C22.2, C23.2
NET_U9_1: C24.1, C25.1, C30.1, U5.16, U9.1
NET_U9_15: C24.2, C25.2
NET_U10_C3: R27.1, U10.C3
NET_U10_C8: R28.1, U10.C8
NET_U14_1: C39.1, R30.1, R31.1, R32.1, R33.1, U14.1, U14.8
NET_U14_2: C38.1, U14.2
NET_U14_3: C39.2, C40.1, C40.2, U14.3
NET_U14_5: R34.1, U14.5
NET_U14_10: C36.1, U14.10
NET_U14_12: C35.1, I1.1, U14.12
NET_U14_14: C35.2, U14.14
NET_U14_15: R35.1, R36.1, U14.15
NET_U14_ATNET_3: I1.2, R30.2
NET_U14_ATNET_4: C40.2, R32.2
NET_U15_1: C47.1, R38.1, R39.1, R40.1, R41.1, U15.1, U15.8
NET_U15_2: C46.1, U15.2
NET_U15_3: C47.2, C48.1, C48.2, U15.3
NET_U15_5: R42.1, U15.5
NET_U15_10: C44.1, U15.10
NET_U15_12: C43.1, I2.1, U15.12
NET_U15_14: C43.2, U15.14
NET_U15_15: R43.1, R44.1, U15.15
NET_U15_ATNET_3: I2.2, R38.2
NET_U15_ATNET_4: C48.2, R40.2
NET_U16_1: R46.1, R47.1, U16.1
NET_U16_3: R48.2, R49.1, U16.3
NET_U16_4: R45.1, U16.4, U19.2
NET_U17_1: R2.1, U17.1, U17.2
PROC_FSMC_D0: U1.61, U10.H4
PROC_FSMC_D1: U1.62, U10.J4
PROC_FSMC_D2: U1.81, U10.K4
PROC_FSMC_D3: U1.82, U10.K5
PROC_FSMC_D4: U1.38, U10.K6
PROC_FSMC_D5: U1.39, U10.J7
PROC_FSMC_D6: U1.40, U10.K7
PROC_FSMC_D7: U1.41, U10.J8
PROC_FSMC_NCE2: R24.1, U1.88, U10.C6
PROC_FSMC_NOE: R25.1, U1.85, U10.D4
PROC_FSMC_NWE: R26.1, U1.86, U10.C7
PROC_I2S2_CK: U1.52, U5.24
PROC_I2S2_SD: U1.54, U5.26
PROC_I2S2_WS: U1.51, U5.23
PROC_SDIO_CK: R17.1, U1.80, U4.5
PROC_SDIO_CMD: R16.1, U1.83, U4.3
PROC_SDIO_D0: R18.1, U1.65, U4.7
PROC_SDIO_D1: R19.1, U1.66, U4.8
PROC_SDIO_D2: R20.1, U1.78, U4.1
PROC_SDIO_D3: R21.1, U1.79, U4.2
VCC_S1_16V8: C37.1, C45.1, C52.1, C53.1, J1.1, R35.2, R43.2, U14.9, U15.9
VCC_TIER1_1V2: C26.1, I1.2, R30.2, U5.30
VCC_TIER1_3V3: C1.1, C2.1, C3.1, C4.1, C5.1, C6.1, C7.1, C8.1, C15.1, C16.1, C17.1, C18.1, C27.1, C28.1, C31.1, C32.1, C33.1, C34.1, C51.1, C54.1, F1.2, I2.2, R4.2, R5.2, R6.2, R7.2, R8.2, R12.2, R13.2, R16.2, R17.2, R18.2, R19.2, R20.2, R21.2, R22.2, R24.2, R25.2, R26.2, R27.2, R28.2, R38.2, R45.2, R46.2, R48.1, U1.6, U1.11, U1.28, U1.50, U1.75, U1.100, U2.8, U3.7, U3.8, U4.4, U5.5, U5.20, U10.H8, U10.J6, U13.4, U16.6, U19.5

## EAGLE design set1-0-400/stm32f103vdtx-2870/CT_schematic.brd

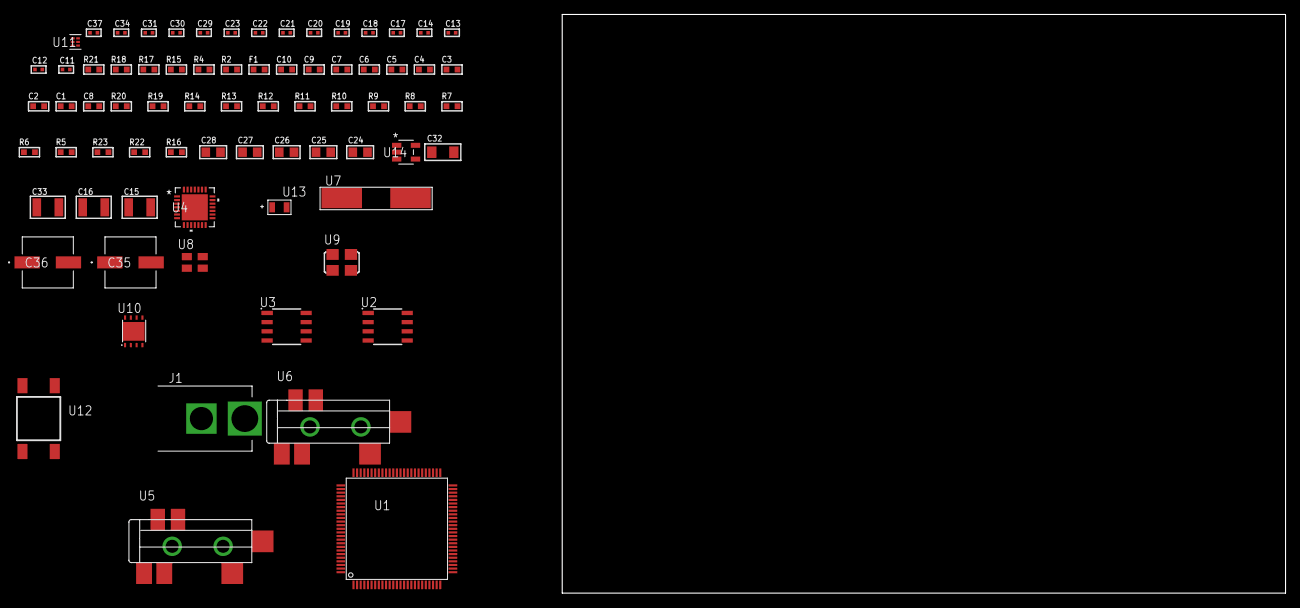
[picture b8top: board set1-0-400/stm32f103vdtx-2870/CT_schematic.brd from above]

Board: 2 copper layers, 100.0 x 80.0 mm, 74 parts (0 on the bottom side), 37 nets, no tracks yet.

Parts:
C1, C10: 1e-06; C0603
C2, C3, C4, C5, C6, C7: 1e-07; C0603
C8: 4.7e-06; C0603
C9: 1e-08; C0603
C11, C12: 1e-11; C0402
C13, C14, C29, C30, C31, C37: 1e-08; C0402
C15, C16: 2.2e-05; C1210
C17, C18: 1e-09; C0402
C19, C20, C21, C22, C23, C34: 1e-07; C0402
C24, C25, C26, C27, C28: 1e-05; C0805
C32: 1e-05; C1206
C33: 1e-05; C1210
C35, C36: 0.0001; EXV-9H
F1: 240.0; L0603
J1: PJ-037B; PJ-037B_PACKAGE
R2, R18: 1000.0; R0603
R4: 4700.0; R0603
R5, R6, R7, R8, R9, R10, R11, R19, R20: 10000.0; R0603
R12, R13, R14: 47000.0; R0603
R15: 680.0; R0603
R16: 100000.0; R0603
R17: 2231.0; R0603
R21: 9100.0; R0603
R22: 680000.0; R0603
R23: 120000.0; R0603
U1: stm32f103vdt6; LQFP100
U2: AT25080B-SSHL-T; SOIC-8
U3: AT25512N-SH-T; SOIC-8
U4: WM8731CLSEFL; QFN-28
U5, U6: SJ-43515TS-SMT-TR
U7: ABLS-25.000MHZ-B2F-T
U8: ASEK-32.768KHz-ECST; ASEK
U9: ASFL1-12.288MHZ-EC-T; ASFL1
U10: LP3878SDX-ADJ/NOPB; WSON-8
U11: TPS3895ADRYR; SON-6
U12: 4-1437565-2; SW_4-1437565-2
U13: Q65110A2395; LGM67K-G1J2-24-Z
U14: nc7sz125m5x; NC7SZ125M5X

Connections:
CLK_CRYSTAL_U1_12: C11.1, U1.12, U7.1
CLK_CRYSTAL_U1_13: C12.1, U1.13, U7.2
CLK_U1_8: U1.8, U8.3
CLK_U4_1: U4.1, U9.3
GND: C1.2, C2.2, C3.2, C4.2, C5.2, C6.2, C7.2, C8.2, C9.2, C10.2, C11.2, C12.2, C13.2, C14.2, C18.2, C19.2, C20.2, C21.2, C22.2, C23.2, C24.2, C25.2, C26.2, C27.2, C28.2, C29.2, C30.2, C31.2, C32.2, C33.2, C34.2, C35.2, C36.2, C37.2, J1.2, R2.2, R5.2, R12.2, R13.2, R14.2, R18.2, R21.2, R23.2, U1.10, U1.19, U1.20, U1.27, U1.49, U1.74, U1.99, U2.4, U3.4, U4.4, U4.15, U4.19, U4.25, U4.26, U4.29, U5.1, U6.1, U8.2, U9.2, U10.3, U10.PAD, U11.2, U13.C, U14.1, U14.3
NET_U1_14: R4.1, U1.14, U14.4
NET_U1_22: C9.1, C10.1, F1.1, U1.21, U1.22
NET_U1_94: R5.1, U1.94
NET_U1_98: U12.3, U12.4
NET_U2_3: R6.1, U2.3
NET_U2_7: R8.1, U2.7
NET_U3_3: R9.1, U3.3
NET_U3_7: R11.1, U3.7
NET_U4_20: C23.1, C28.1, U4.20
NET_U5_2: C16.1, R13.1, U5.2
NET_U5_5: C15.1, R12.1, U5.5
NET_U6_5: C17.1, C18.1, R14.1, R15.1, U6.5
NET_U10_1: C31.1, U10.1
NET_U10_6: R17.2, R18.1, U10.6
NET_U10_8: R16.1, U10.8
NET_U11_1: R20.1, R21.1, U11.1
NET_U11_3: R22.2, R23.1, U11.3
NET_U11_4: R19.1, U11.4, U14.2
NET_U12_1: R2.1, U12.1, U12.2
PROC_I2S3_CK: U1.89, U4.7
PROC_I2S3_SD: U1.91, U4.8
PROC_I2S3_WS: U1.77, U4.9, U4.11
PROC_SPI1_MISO: U1.31, U3.2
PROC_SPI1_MOSI: U1.32, U3.5
PROC_SPI1_NSS: R10.1, U1.29, U3.1
PROC_SPI1_SCK: U1.30, U3.6
PROC_SPI2_MISO: U1.53, U2.2
PROC_SPI2_MOSI: U1.54, U2.5
PROC_SPI2_NSS: R7.1, U1.51, U2.1
PROC_SPI2_SCK: U1.52, U2.6
VCC_S1_6V2: C32.1, C35.1, C36.1, J1.1, R16.2, U10.4
VCC_TIER1_3V3: C1.1, C2.1, C3.1, C4.1, C5.1, C6.1, C7.1, C8.1, C13.1, C14.1, C19.1, C20.1, C21.1, C22.1, C24.1, C25.1, C26.1, C27.1, C29.1, C30.1, C33.1, C34.1, C37.1, F1.2, R4.2, R6.2, R7.2, R8.2, R9.2, R10.2, R11.2, R17.1, R19.2, R20.2, R22.1, U1.6, U1.11, U1.28, U1.50, U1.75, U1.100, U2.8, U3.8, U4.3, U4.5, U4.12, U4.18, U8.4, U9.4, U10.5, U11.6, U14.5
